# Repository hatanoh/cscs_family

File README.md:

# cscs_family
cscs64 / cscs52 keyboards 

cscsファミリは、中心部に記号向けの6つのキーがあるのが特徴のキーボードで、mteiさんの[semi ergo](https://github.com/mtei/SemiErgo_Layout)フォーマットを参考にしています。

また昇圧回路を搭載し単4電池1本で[BLE Micro Pro](https://github.com/sekigon-gonnoc/BLE-Micro-Pro)を使用できるのも特徴の一つです。

# ビルドガイド
[Build Guide](https://github.com/hatanoh/cscs_family/blob/master/Doc/buildguide.md)

# ファームウェア
[Firmware/BLE Micro Pro](https://github.com/hatanoh/qmk_firmware)

# デフォルトのキー配置

ペアリング関係のキーは[ペアリング/接続先切り替えの設定](https://github.com/hatanoh/cscs_family/blob/master/Doc/pairing.md)を参照

詳細はファームウェアの
[キーマップ(cscs64)](https://github.com/hatanoh/qmk_firmware/blob/nrf52/keyboards/cscs64_ble/keymaps/cscs64/keymap.c)や
[キーマップ(cscs52)](https://github.com/hatanoh/qmk_firmware/blob/nrf52/keyboards/cscs64_ble/keymaps/cscs52/keymap.c)
を参照のこと。

# FAQ
[FAQ](https://github.com/hatanoh/cscs_family/blob/master/FAQ.md) (背景など/役に立ちません)

BLE Micro Proの[FAQ](https://github.com/sekigon-gonnoc/BLE-Micro-Pro/blob/master/FAQ.md)も参照して下さい。

サリチル酸さんの[Bluetooth接続用のProMicro互換ボード「BLE Micro Pro」の話](https://salicylic-acid3.hatenablog.com/entry/BMP-Introduction)も非常に参考になります。

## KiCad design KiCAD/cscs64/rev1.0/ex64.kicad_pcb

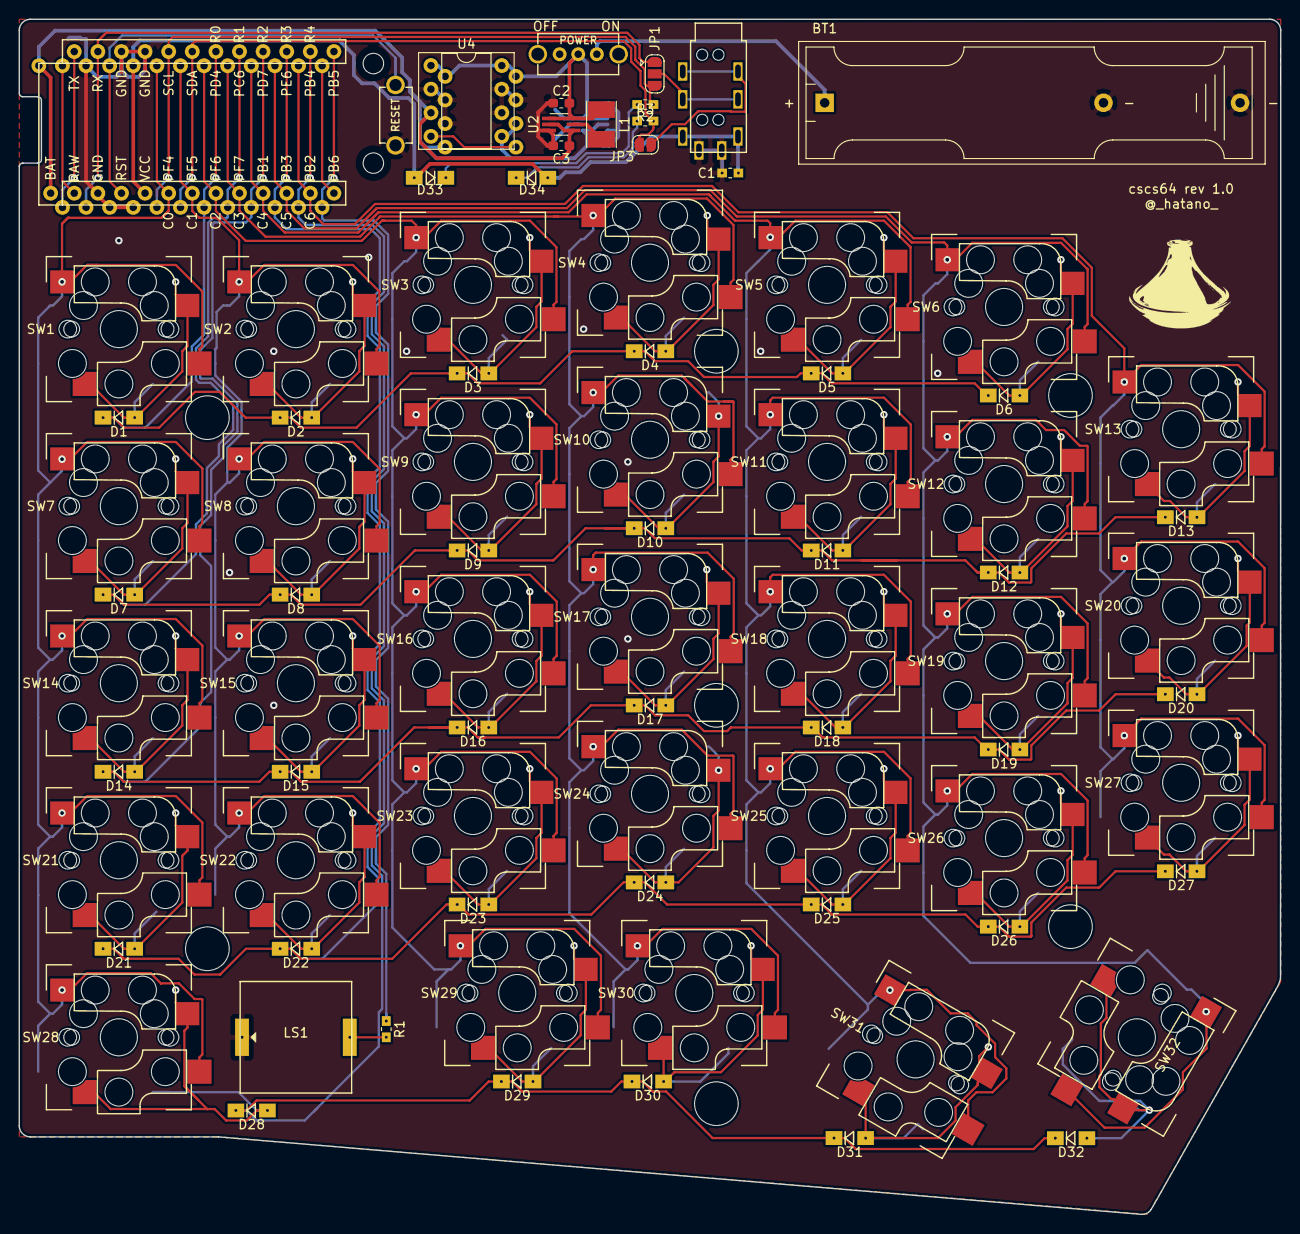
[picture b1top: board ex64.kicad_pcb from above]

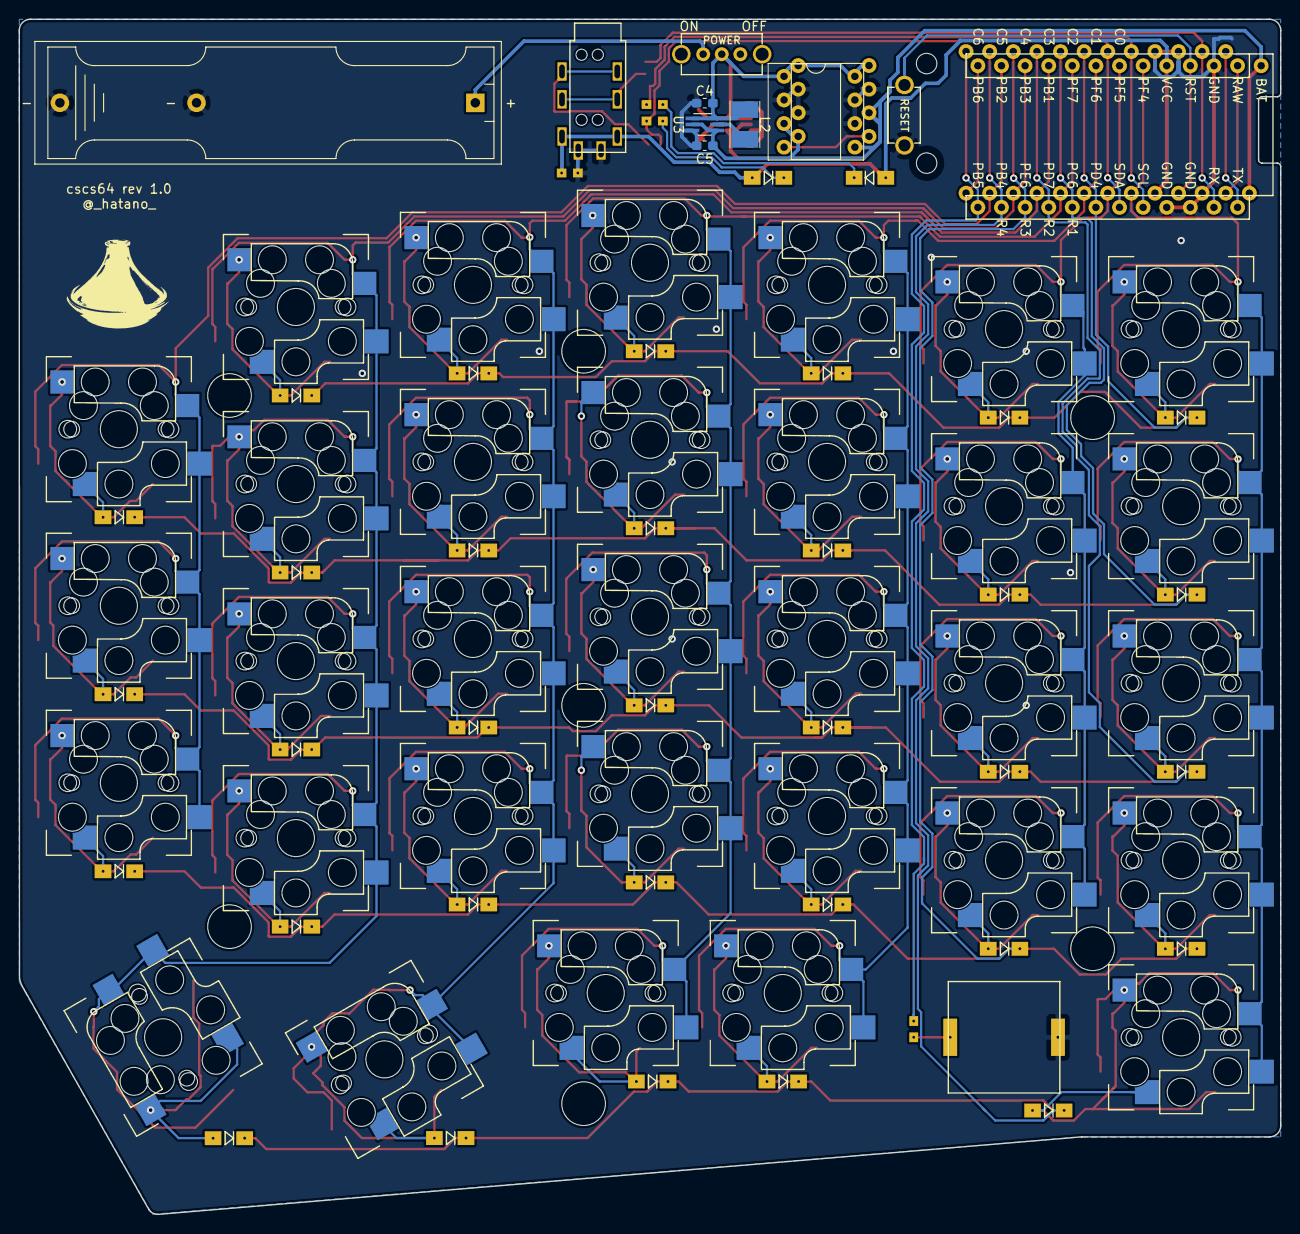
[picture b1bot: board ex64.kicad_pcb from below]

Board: 2 copper layers, 135.7 x 128.6 mm, 96 parts (4 on the bottom side), 61 nets.

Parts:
BT1: Battery_Cell; BatteryHolder_Keystone_2466_1xAAA_reversible
C1: 1u; C_1608SMD_reversible
C2, C3, C4, C5: 10uF; C_0603_1608Metric_Pad1.05x0.95mm_HandSolder
D1, D2, D3, D4, D5, D6, D7, D8, D9, D10, D11, D12, D13, D14, D15, D16, D17, D18, D19, D20, D21, D22, D23, D24, D25, D26, D27, D28, D29, D30, D31, D32, D33, D34: D; Diode_SOD123_Reversible
H1, H2, H3, H4, H5, H6, H7: MountingHole; HOLE_M2_TH
H8, H9: MountingHole; HOLE_M2
J1: I2C#1; TRRS_JACK_MJ4PP9
JP1: JP R1; SolderJumper-3_P1.3mm_Open_RoundedPad1.0x1.5mm
JP3: JP R2; SolderJumper-2_P1.3mm_Open_RoundedPad1.0x1.5mm
L1, L2: 4.7uH; L_Taiyo-Yuden_NR-30xx_HandSoldering
LS1: Speaker; PKLCS1212E4001
R1: 1k; R_1608SMD_reversible
R2, R3: 2.2k; R_1608SMD_reversible
SW1, SW2, SW3, SW4, SW5, SW6, SW7, SW8, SW9, SW10, SW11, SW12, SW13, SW14, SW15, SW16, SW17, SW18, SW19, SW20, SW21, SW22, SW23, SW24, SW25, SW26, SW27, SW28, SW29, SW30, SW31: SW_Push; CPG151101S11_reversible3
SW32: SW_Push; CPG151101S11_reversible3_1.50h
SW33: SW_RST; TACT_SWITCH_TVBP06
SW34: SW_PWR; SLIDE_SWITCH_SK-12D01
U1: BLE-Micro-Pro-2; BLEMicroPro-2
U2, U3: TPS61221; SOT-363_SC-70-6_Handsoldering
U4: M-05720

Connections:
BAT: C3.1, C5.1, U1.25, U2.2, U2.4, U3.2, U3.4, U4.3, U4.5
C0: SW1.1, SW7.1, SW14.1, SW21.1, SW28.1, U1.20
C1: SW2.1, SW8.1, SW15.1, SW22.1, U1.19
C2: SW3.1, SW9.1, SW16.1, SW23.1, SW29.1, U1.18
C3: SW4.1, SW10.1, SW17.1, SW24.1, SW30.1, U1.17
C4: SW5.1, SW11.1, SW18.1, SW25.1, SW31.1, U1.16
C5: SW6.1, SW12.1, SW19.1, SW26.1, SW32.1, U1.15
C6: SW13.1, SW20.1, SW27.1, U1.14
GND: BT1.2, C1.2, C2.2, C3.2, C4.2, C5.2, J1.S, LS1.2, SW33.2, U1.3, U1.4, U1.23, U2.3, U3.3, U4.2, U4.6, U4.7
unnamed: BT1.1, SW34.2
unnamed: D1.2, SW1.2
unnamed: D2.2, SW2.2
unnamed: D3.2, SW3.2
unnamed: D4.2, SW4.2
unnamed: D5.2, SW5.2
unnamed: D6.2, SW6.2
unnamed: D7.2, SW7.2
unnamed: D8.2, SW8.2
unnamed: D9.2, SW9.2
unnamed: D10.2, SW10.2
unnamed: D11.2, SW11.2
unnamed: D12.2, SW12.2
unnamed: D13.2, SW13.2
unnamed: D14.2, SW14.2
unnamed: D15.2, SW15.2
unnamed: D16.2, SW16.2
unnamed: D17.2, SW17.2
unnamed: D18.2, SW18.2
unnamed: D19.2, SW19.2
unnamed: D20.2, SW20.2
unnamed: D21.2, SW21.2
unnamed: D22.2, SW22.2
unnamed: D23.2, SW23.2
unnamed: D24.2, SW24.2
unnamed: D25.2, SW25.2
unnamed: D26.2, SW26.2
unnamed: D27.2, SW27.2
unnamed: D28.2, SW28.2
unnamed: D29.2, SW29.2
unnamed: D30.2, SW30.2
unnamed: D31.2, SW31.2
unnamed: D32.2, SW32.2
unnamed: D33.1, R2.1
unnamed: D34.1, R3.1
unnamed: J1.R1, JP1.2
unnamed: J1.R2, JP3.1
unnamed: L1.1, U2.5
unnamed: L2.1, U3.5
unnamed: LS1.1, R1.2
R0: D1.1, D2.1, D3.1, D4.1, D5.1, D6.1, U1.7
R1: D7.1, D8.1, D9.1, D10.1, D11.1, D12.1, D13.1, U1.8
R2: D14.1, D15.1, D16.1, D17.1, D18.1, D19.1, D20.1, U1.9
R3: D21.1, D22.1, D23.1, D24.1, D25.1, D26.1, D27.1, U1.10
R4: D28.1, D29.1, D30.1, D31.1, D32.1, U1.11
RST: SW33.1, U1.22
SCL: JP1.3, R2.2, U1.5
SDA: JP3.2, R3.2, U1.6
VCC: C1.1, D33.2, D34.2, J1.T, U1.21
buzz: R1.1, U1.12
cell: C2.1, C4.1, L1.2, L2.2, SW34.1, U2.1, U2.6, U3.1, U3.6, U4.1, U4.8
data: JP1.1, U1.2

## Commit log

2019-05-27 correct markdown
2019-05-28 remove logo
2019-05-30 Rename bulidguide.md to buildguide.md
2019-05-30 add pairing.md
2019-05-30 add cscs64 keymap image
